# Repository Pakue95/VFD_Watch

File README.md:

# VFD Watch Project

This project was originally inspired by Johngineer's [ChronodeVFD](https://blog.adafruit.com/2014/10/29/chronodevfd-a-watch-by-johngineer-wearablewednesday/) project. However no concrete design information were available therefore this project was born.

The goal was to create a mobile driver circuit for the common IVL2-5/7 vacuum fluorescent display, that is powered by a single cell battery. The datasheet of the display can be found on the [Loststreak](http://loststeak.com/ivl2-75-vfd-datasheets/) blog.

## Circuit elements

### Microcontroller
An **ESP32 WROOM-32** module is used as a microcontroller for the display and wireless communication. It is interfaced fo r programming via a **FT231XS** USB-Serial converter.

### Battery voltage regulation
The choice for the battery driver IC fell on the **MP3120** single cell 1.2A step up module as it can handle very low battery voltages and still start up. If wireless communication is used during the power up of the display the step-up module won't be able to supply enough power from a normal Alkaline cell to the ESP32 and a brownout reset will occur. Primary lithium cells, 2 Alkaline batteries or LiIon should be sufficient to power all functions at the same time.

### VFD driver
The display is driven by a 24V rail from a **MCP1663** step-up converter and high-side switches (**TBD62783A**) to power the segments. The filament is driven from the 3.3V rail and pulse-modulated from a motor H-bridge driver (**DRV8837C**) to achieve an equivalent to the 2.4V @ 60mA power conditions described in the datasheet. The H-bridge design allows an equal brightness of the characters without the use of a complex center-tapped AC circuit.

## Software

### Functions

```cpp
void begin(uint8_t dutyCycle, uint32_t freqMultiplex, uint32_t freqHeat)
```

* ```dutyCycle``` sets the PWM duty cycle of the heating filament. 0-255; typical 120.
* ```freqMultiplex``` sets the rate at which the characters are cycled though (1kHz -> 200Hz total refresh of the display). The timing is controlled in the background by an interrupt function that calls for an update of the currently displayed character. This process runs on core 0 of the ESP32, therefore during WiFi use the display can flicker a bit.
* ```freqHeat``` sets the frequency of the heating filament PWM. The value should be in the kHz range.

```cpp
void deactivate()
```
Turns of the heating filament and the 24V rail to preserve power.

```cpp
void activate()
```
Turns the display back on after a ```deactivate()```.

```cpp
void setHours(uint8_t hours)
```
Sets the first two digits. Range 0-99.

```cpp
void setMinutes(uint8_t minutes)
```
Sets the last two digits. Range 0-99.

```cpp
void setCharacter(char character, int pos)
```
Displays a char (```a-z; 0-9; '-'```) at position ```pos``` (```0-3```)

```cpp
void print(char* text)
```
Similar to ```setCharacter()``` but it displays the first 4 chars of the array.

```cpp
void setSegment(uint8_t segments, uint8_t pos);
```
Sets specific segments of a digit through the use of a byte mask (least to most significant bit). E.g. ```0b00101000``` would set segments ```d``` & ```f```. ```pos``` declares the digit to be changed (```0-3```).

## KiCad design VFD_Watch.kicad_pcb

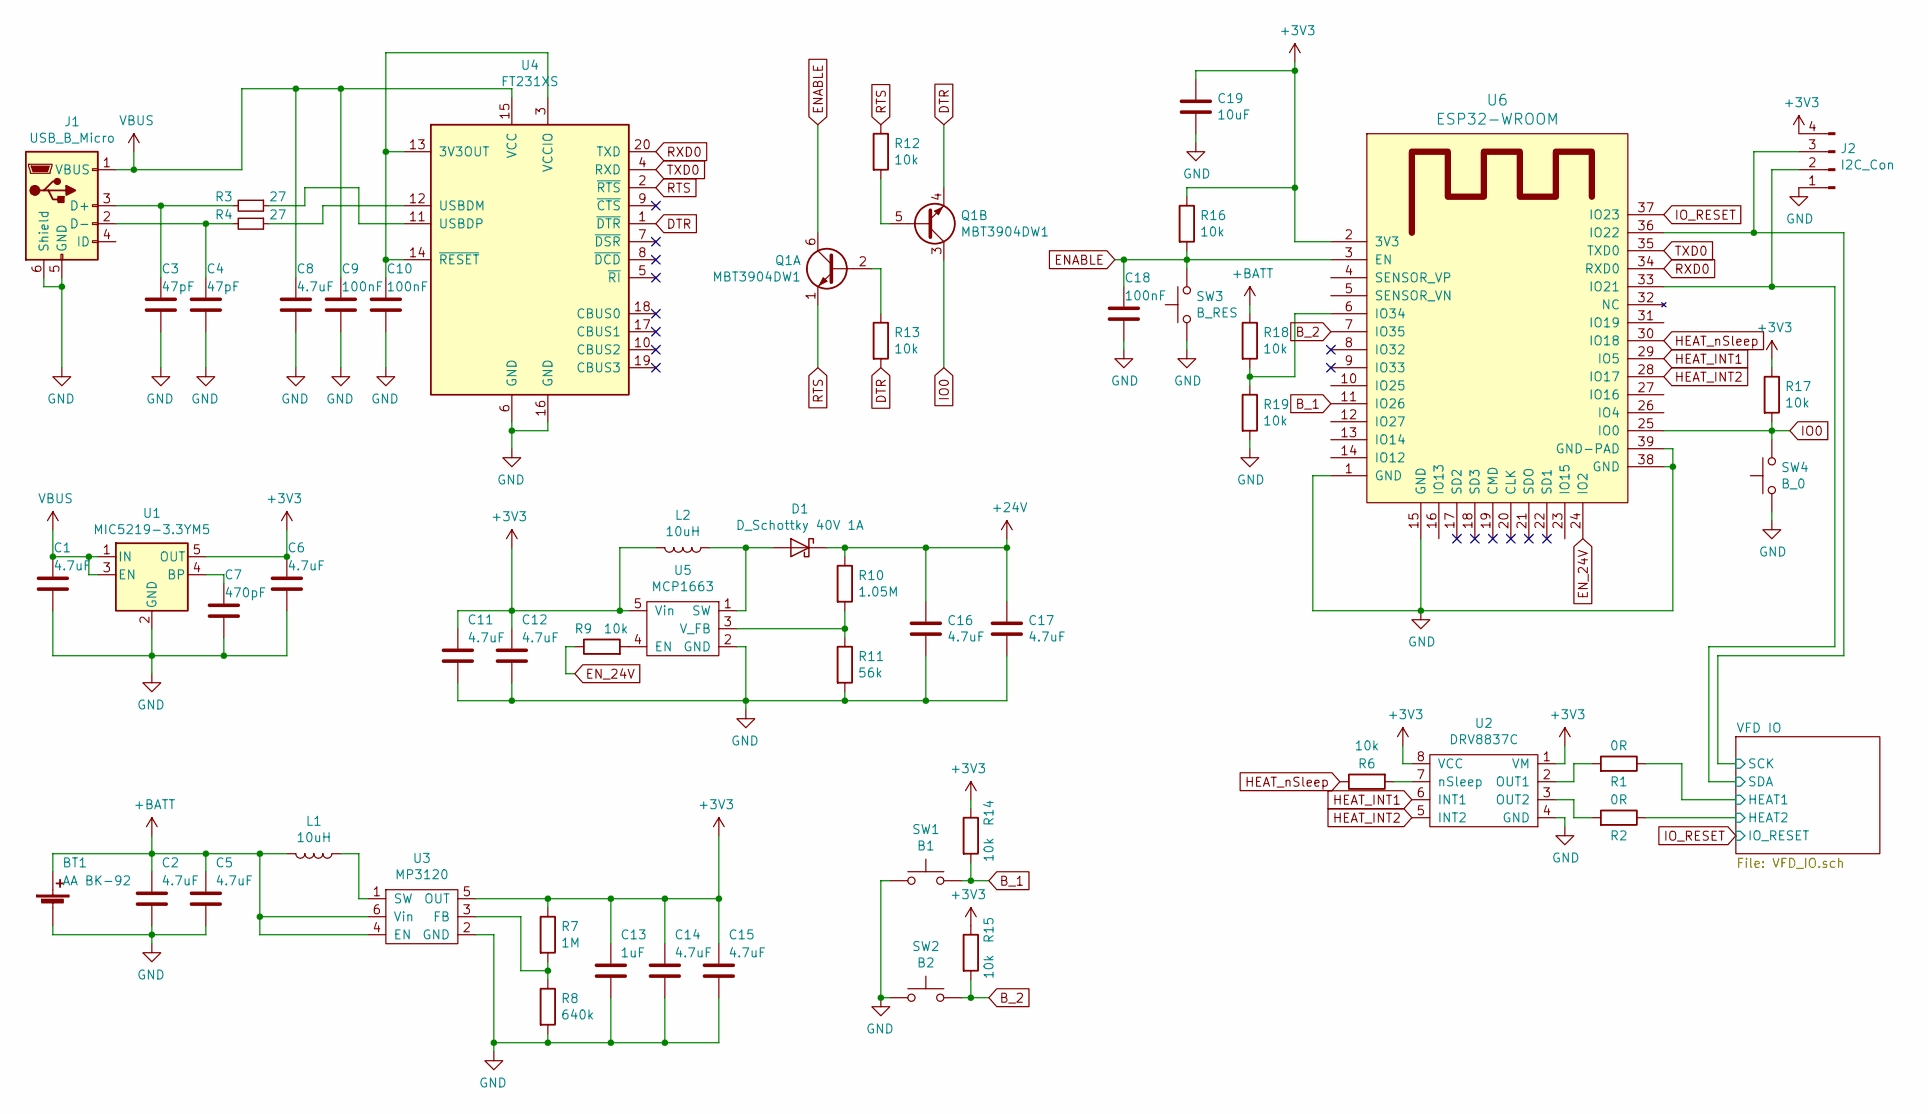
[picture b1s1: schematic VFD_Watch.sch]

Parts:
BT1: AA BK-92; BK-92
C1, C2, C5, C6, C8, C11, C12, C14, C15, C16, C17: 4.7uF; C_0805_2012Metric
C3, C4: 47pF; C_0805_2012Metric
C7: 470pF; C_0805_2012Metric
C9, C10, C18: 100nF; C_0805_2012Metric
C13: 1uF; C_0805_2012Metric
C19: 10uF; C_1206_3216Metric
D1: D_Schottky 40V 1A; D_SOD-323
J1: USB_B_Micro; USB_Micro-B_Molex_47346-0001
J2: I2C_Con; PinHeader_1x04_P1.27mm_Vertical
L1, L2: 10uH; L_Taiyo-Yuden_MD-5050
Q1: MBT3904DW1; SOT-363_SC-70-6
R1, R2: 0R; R_1206_3216Metric
R3, R4: 27; R_0805_2012Metric
R6, R9, R12, R13, R14, R15, R16, R17, R18, R19: 10k; R_0805_2012Metric
R7: 1M; R_0805_2012Metric
R8: 640k; R_0805_2012Metric
R10: 1.05M; R_0805_2012Metric
R11: 56k; R_0805_2012Metric
SW1: B1; SW_SPST_EVQP7A
SW2: B2; SW_SPST_EVQP7A
SW3: B_RES; SW_SPST_EVQP7A
SW4: B_0; SW_SPST_EVQP7A
U1: MIC5219-3.3YM5; SOT-23-5
U2: DRV8837C; WSON-8-1EP_2x2mm_P0.5mm_EP0.9x1.6mm
U3: MP3120; TSOT-23-6
U4: FT231XS; SSOP-20_3.9x8.7mm_P0.635mm
U5: MCP1663; TSOT-23-5
U6: ESP32-WROOM

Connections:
+3V3: C6.1, C11.1, C12.1, C13.1, C14.1, C15.1, C19.1, J2.4, L2.2, R7.1, R14.1, R15.1, R16.1, R17.1, U1.5 (OUT), U2.1 (VM), U2.8 (VCC), U3.5 (OUT), U5.5 (Vin), U6.2 (3V3); also elsewhere on the board
+24V: C16.1, C17.1, D1.1 (K), R10.1; also elsewhere on the board
+BATT: BT1.1 (+), C2.1, C5.1, L1.2, R18.1, U3.4 (EN), U3.6 (Vin)
/VFD IO/HEAT1: R1.1; also elsewhere on the board
/VFD IO/HEAT2: R2.1; also elsewhere on the board
/VFD IO/SCK: J2.3, U6.36 (IO22); also elsewhere on the board
/VFD IO/SDA: J2.2, U6.33 (IO21); also elsewhere on the board
B_1: R14.2, SW1.2, U6.11 (IO26)
B_2: R15.2, SW2.2, U6.7 (IO35)
DTR: Q1.4 (E2), R13.2, U4.1 (~DTR)
ENABLE: C18.1, Q1.6 (C1), R16.2, SW3.2, U6.3 (EN)
EN_24V: R9.1, U6.24 (IO2)
GND: BT1.2 (-), C1.2, C2.2, C3.2, C4.2, C5.2, C6.2, C7.2, C8.2, C9.2, C10.2, C11.2, C12.2, C13.2, C14.2, C15.2, C16.2, C17.2, C18.2, C19.2, J1.5 (GND), J1.6 (Shield), J2.1, R8.2, R11.2, R19.2, SW1.1, SW2.1, SW3.1, SW4.1, U1.2 (GND), U2.4 (GND), U2.9 (GND), U3.2 (GND), U4.6 (GND), U4.16 (GND), U5.2 (GND), U6.1 (GND), U6.15 (GND), U6.38 (GND), U6.39 (GND-PAD); also elsewhere on the board
HEAT_INT1: U2.6 (INT1), U6.29 (IO5)
HEAT_INT2: U2.5 (INT2), U6.28 (IO17)
HEAT_nSleep: R6.1, U6.30 (IO18)
IO0: Q1.3 (C2), R17.2, SW4.2, U6.25 (IO0)
IO_RESET: U6.37 (IO23); also elsewhere on the board
unnamed: C3.1, J1.3 (D+), R3.2
unnamed: C4.1, J1.2 (D-), R4.2
unnamed: C7.1, U1.4 (BP)
unnamed: C10.1, U4.3 (VCCIO), U4.13 (3V3OUT), U4.14 (~RESET)
unnamed: D1.2 (A), L2.1, U5.1 (SW)
unnamed: L1.1, U3.1 (SW)
unnamed: Q1.2 (B1), R13.1
unnamed: Q1.5 (B2), R12.2
unnamed: R1.2, U2.2 (OUT1)
unnamed: R2.2, U2.3 (OUT2)
unnamed: R3.1, U4.11 (USBDP)
unnamed: R4.1, U4.12 (USBDM)
unnamed: R6.2, U2.7 (nSleep)
unnamed: R7.2, R8.1, U3.3 (FB)
unnamed: R9.2, U5.4 (EN)
unnamed: R10.2, R11.1, U5.3 (V_FB)
unnamed: R18.2, R19.1, U6.6 (IO34)
RTS: Q1.1 (E1), R12.1, U4.2 (~RTS)
RXD0: U4.20 (TXD), U6.34 (RXD0)
TXD0: U4.4 (RXD), U6.35 (TXD0)
VBUS: C1.1, C8.1, C9.1, J1.1 (VBUS), U1.1 (IN), U1.3 (EN), U4.15 (VCC)

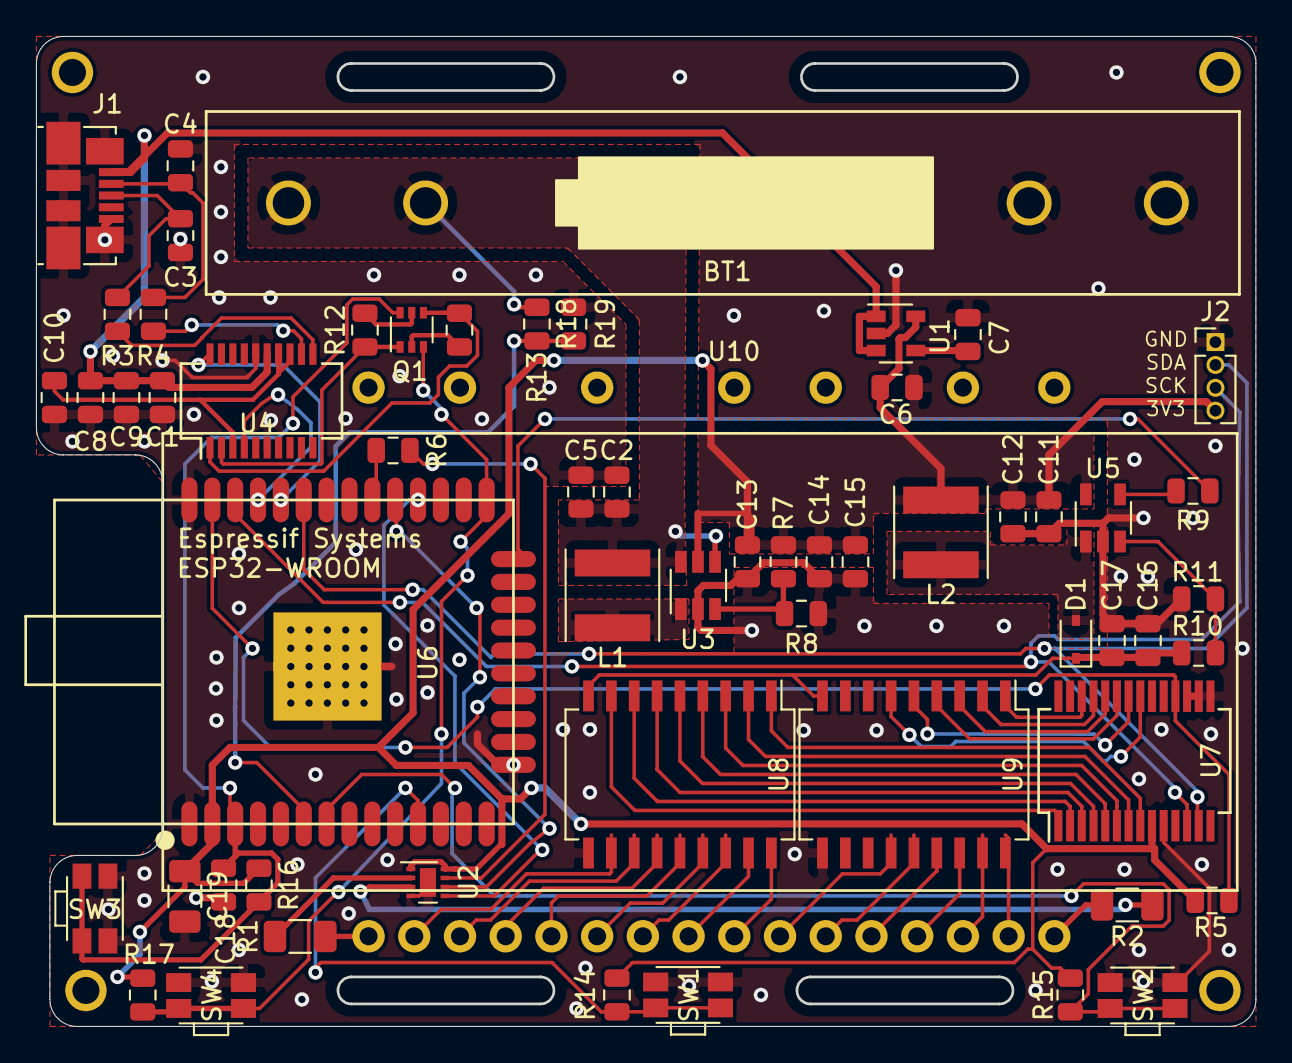
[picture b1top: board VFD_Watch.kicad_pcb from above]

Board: 2 copper layers, 67.7 x 54.9 mm, 59 parts (0 on the bottom side), 67 nets.

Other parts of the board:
R5: 10k; R_0805_2012Metric
U7: MCP23017_SS; SSOP-28_5.3x10.2mm_P0.65mm
U8, U9: TBD62783A; SOP-18_7.0x12.5mm_P1.27mm
U10: IVL2-7_5; ILV2-5_7

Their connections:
+3V3: R5.1, U7.9; also elsewhere on the board
+24V: U8.9, U9.9; also elsewhere on the board
/VFD IO/GPA0: U7.21, U9.6
/VFD IO/GPA1: U7.22, U9.5
/VFD IO/GPA2: U7.23, U9.4
/VFD IO/GPA3: U7.24, U9.3
/VFD IO/GPA4: U7.25, U9.2
/VFD IO/GPA5: U7.26, U9.1
/VFD IO/GPB0: U7.1, U8.8
/VFD IO/GPB1: U7.2, U8.7
/VFD IO/GPB2: U7.3, U8.6
/VFD IO/GPB3: U7.4, U8.5
/VFD IO/GPB4: U7.5, U8.4
/VFD IO/GPB5: U7.6, U8.3
/VFD IO/GPB6: U7.7, U8.2
/VFD IO/GPB7: U7.8, U8.1
/VFD IO/HEAT1: U10.1; also elsewhere on the board
/VFD IO/HEAT2: U10.16; also elsewhere on the board
/VFD IO/HSS_01: U8.18, U10.9
/VFD IO/HSS_02: U8.17, U10.8
/VFD IO/HSS_03: U8.16, U10.7
/VFD IO/HSS_04: U8.15, U10.6
/VFD IO/HSS_05: U8.14, U10.5
/VFD IO/HSS_06: U8.13, U10.4
/VFD IO/HSS_07: U8.12, U10.3
/VFD IO/HSS_08: U8.11, U10.2
/VFD IO/HSS_09: U9.18, U10.15
/VFD IO/HSS_10: U9.17, U10.14
/VFD IO/HSS_11: U9.16, U10.13
/VFD IO/HSS_12: U9.15, U10.12
/VFD IO/HSS_13: U9.14, U10.11
/VFD IO/HSS_14: U9.13, U10.10
/VFD IO/SCK: U7.12; also elsewhere on the board
/VFD IO/SDA: U7.13; also elsewhere on the board
GND: U7.10, U7.15, U7.16, U7.17, U8.10, U9.10; also elsewhere on the board
IO_RESET: R5.2, U7.18; also elsewhere on the board

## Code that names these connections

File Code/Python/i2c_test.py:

from machine import *
import mcp

pin_24V = Pin(2, Pin.OUT)
pin_HEAT_nSleep = Pin(18, Pin.OUT)
pin_HEAT_INT1 = Pin(5, Pin.OUT)
pin_HEAT_INT2 = Pin(17, Pin.OUT)

io = mcp.MCP23017(gpioScl=22, gpioSda=21)

for pin in range(0,16):
    io.setup(pin, mcp.OUT)

pin_24V.value(1)
pin_HEAT_nSleep.value(1)
pin_HEAT_INT1.value(1)
HEAT2_PWM = PWM(pin_HEAT_INT2)
HEAT2_PWM.freq(1000)
HEAT2_PWM.duty(200)

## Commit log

2018-11-30 inital commit
2018-12-04 corrected VFD segment labeling
2018-12-05 added PDF schematic
2018-12-06 updated gitignore
2018-12-06 Synced remaining files
2018-12-06 moved multiplex to static member function
2018-12-07 fixed csv
2018-12-07 fixed csv again
2018-12-13 added some new character display functionality and custom segments for animations
2018-12-13 added README.md
2018-12-27 added some wifi search animation
2018-12-29 fixed numbers as characters display
2018-12-30 started to change the byte-based data type to a struct to improve member function compatibility.
2018-12-30 fully converted to the new struct data type
2018-12-30 fixed the compiler warnings and removes unused functions
2019-02-18 fixed BAT INPUT to allow for LiPo voltages without damaging the ESP32, cleaned up silkscreen, updated graphics
2019-05-06 updated Gerbers
2019-05-06 exported RS-274x gerber format
2019-05-08 added edge cuts lines to the strap slots
2019-05-08 last save
2019-05-11 added password example file and removed some 35C5 specific code.
2021-03-14 added a way to set the time with the buttons, once wifi fails
